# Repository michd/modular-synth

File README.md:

# Modular Synthesizer

My fiancee and I plan to build a modular synthesizer, for fun. Here's a repository to hold all kinds of stuff to do with that. I imagine it'll hold the following

- Schematic designs
- PCB designs derived from those schematic design
- Some 3D modeling for related hardware
- Any microcontroller code

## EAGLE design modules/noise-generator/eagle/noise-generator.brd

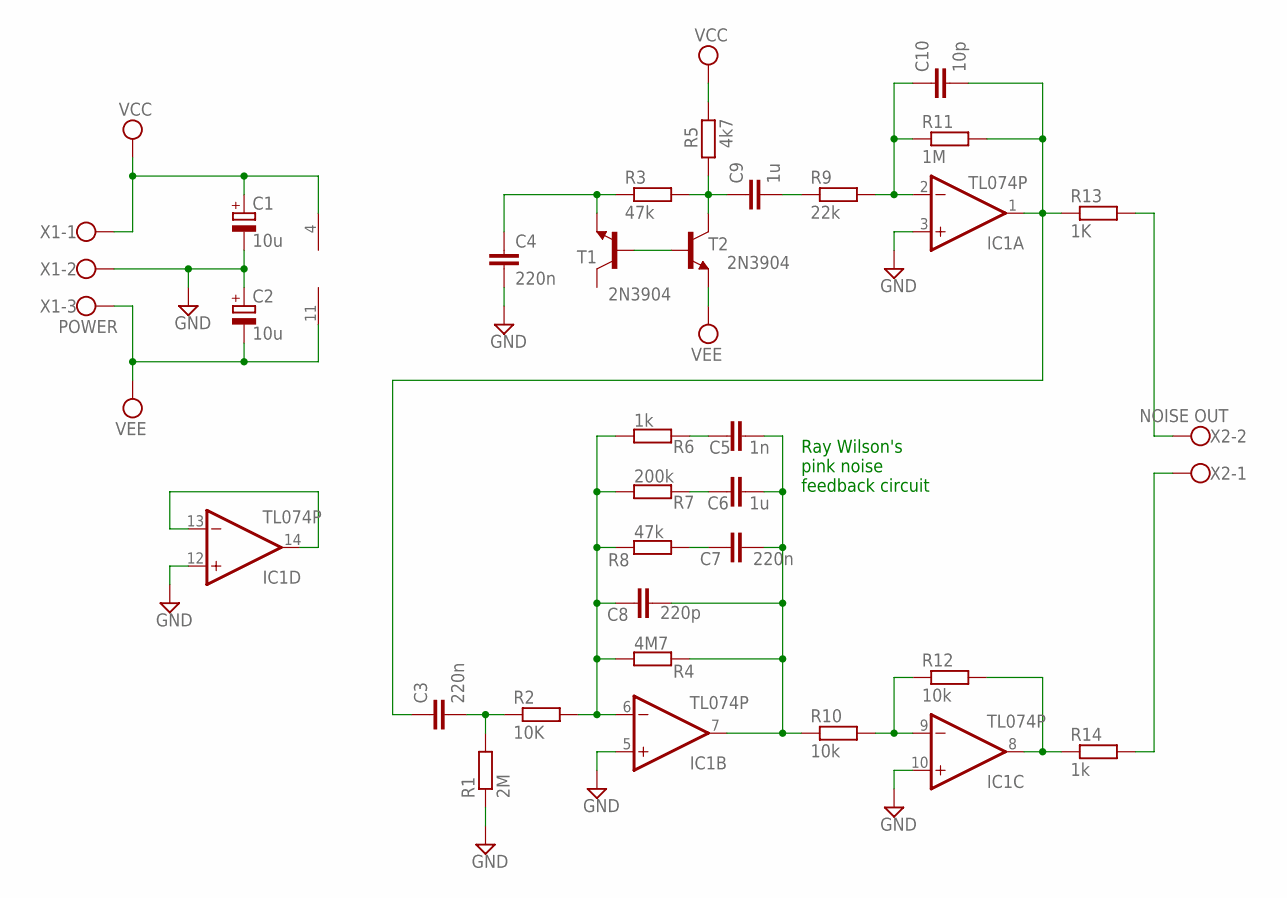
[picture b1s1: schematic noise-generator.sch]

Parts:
C1, C2: 10u; E1,8-4
C3, C4, C7: 220n; C050-024X044
C5: 1n; C050-024X044
C6, C9: 1u; C050-024X044
C8: 220p; C050-024X044
C10: 10p; C025-024X044
IC1: TL074P; DIL14
R1: 2M; 0204/7
R2: 10K; 0204/7
R3, R8: 47k; 0204/7
R4: 4M7; 0204/7
R5: 4k7; 0204/7
R6, R14: 1k; 0204/7
R7: 200k; 0204/7
R9: 22k; 0204/7
R10, R12: 10k; 0204/7
R11: 1M; 0204/7
R13: 1K; 0204/7
T1, T2: 2N3904; TO92
X1: POWER; W237-103
X2: NOISE OUT; W237-102

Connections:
GND: C1.-, C2.+, C4.2, IC1.3 (+IN), IC1.5 (+IN), IC1.10 (+IN), IC1.12 (+IN), R1.1, X1.2
unnamed: C4.1, R3.1, T1.3 (E)
unnamed: IC1.9 (-IN), R10.2, R12.1
unnamed: C9.1, R3.2, R5.1, T2.1 (C)
unnamed: T1.2 (B), T2.2 (B)
unnamed: C9.2, R9.1
unnamed: C10.1, IC1.2 (-IN), R9.2, R11.1
unnamed: R13.2, X2.2
unnamed: C3.1, C10.2, IC1.1 (OUT), R11.2, R13.1
unnamed: IC1.8 (OUT), R12.2, R14.1
unnamed: R14.2, X2.1
unnamed: C8.1, IC1.6 (-IN), R2.2, R4.1, R6.1, R7.1, R8.1
unnamed: C3.2, R1.2, R2.1
unnamed: IC1.13 (-IN), IC1.14 (OUT)
unnamed: C6.1, R7.2
unnamed: C5.1, R6.2
unnamed: C7.1, R8.2
unnamed: C5.2, C6.2, C7.2, C8.2, IC1.7 (OUT), R4.2, R10.1
VCC: C1.+, IC1.4 (V+), R5.2, X1.1
VEE: C2.-, IC1.11 (V-), T2.3 (E), X1.3

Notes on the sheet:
Ray Wilson's pink noise feedback circuit

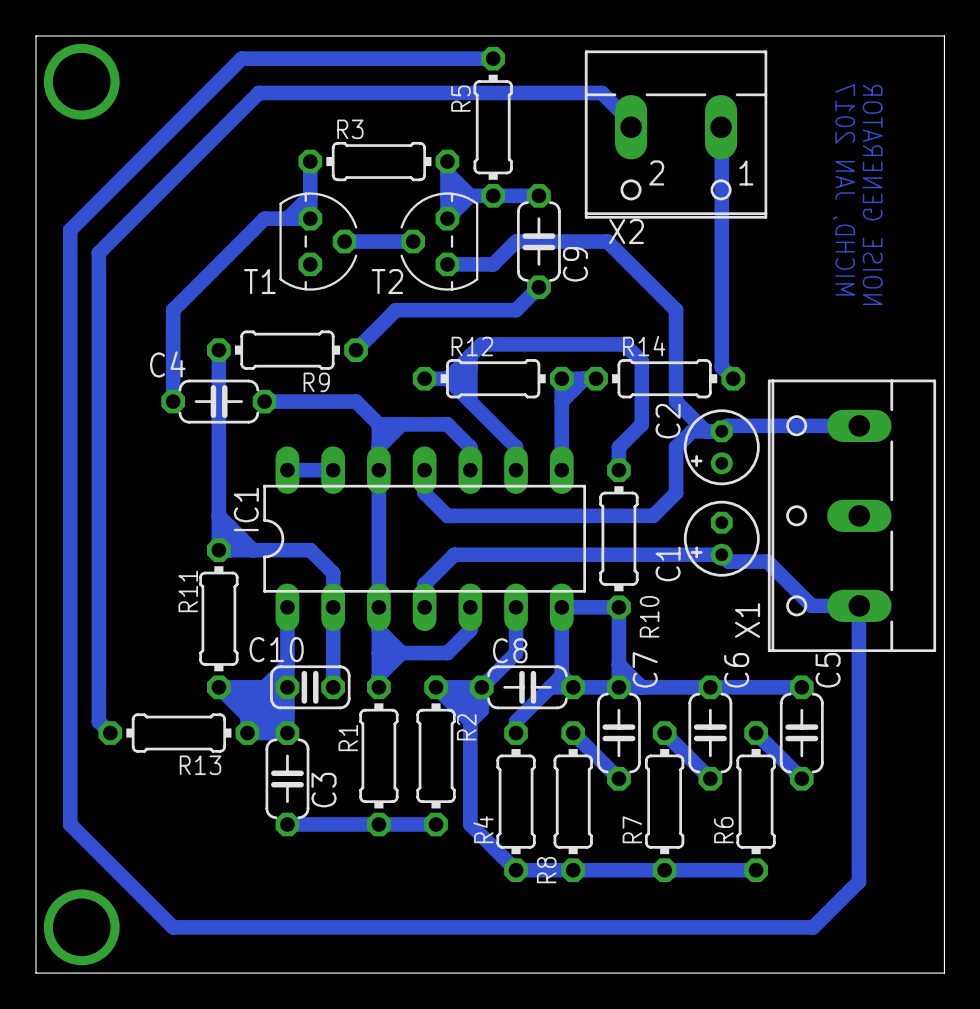
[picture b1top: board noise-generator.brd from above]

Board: 2 copper layers, 50.5 x 52.1 mm, 29 parts (0 on the bottom side), 20 nets.

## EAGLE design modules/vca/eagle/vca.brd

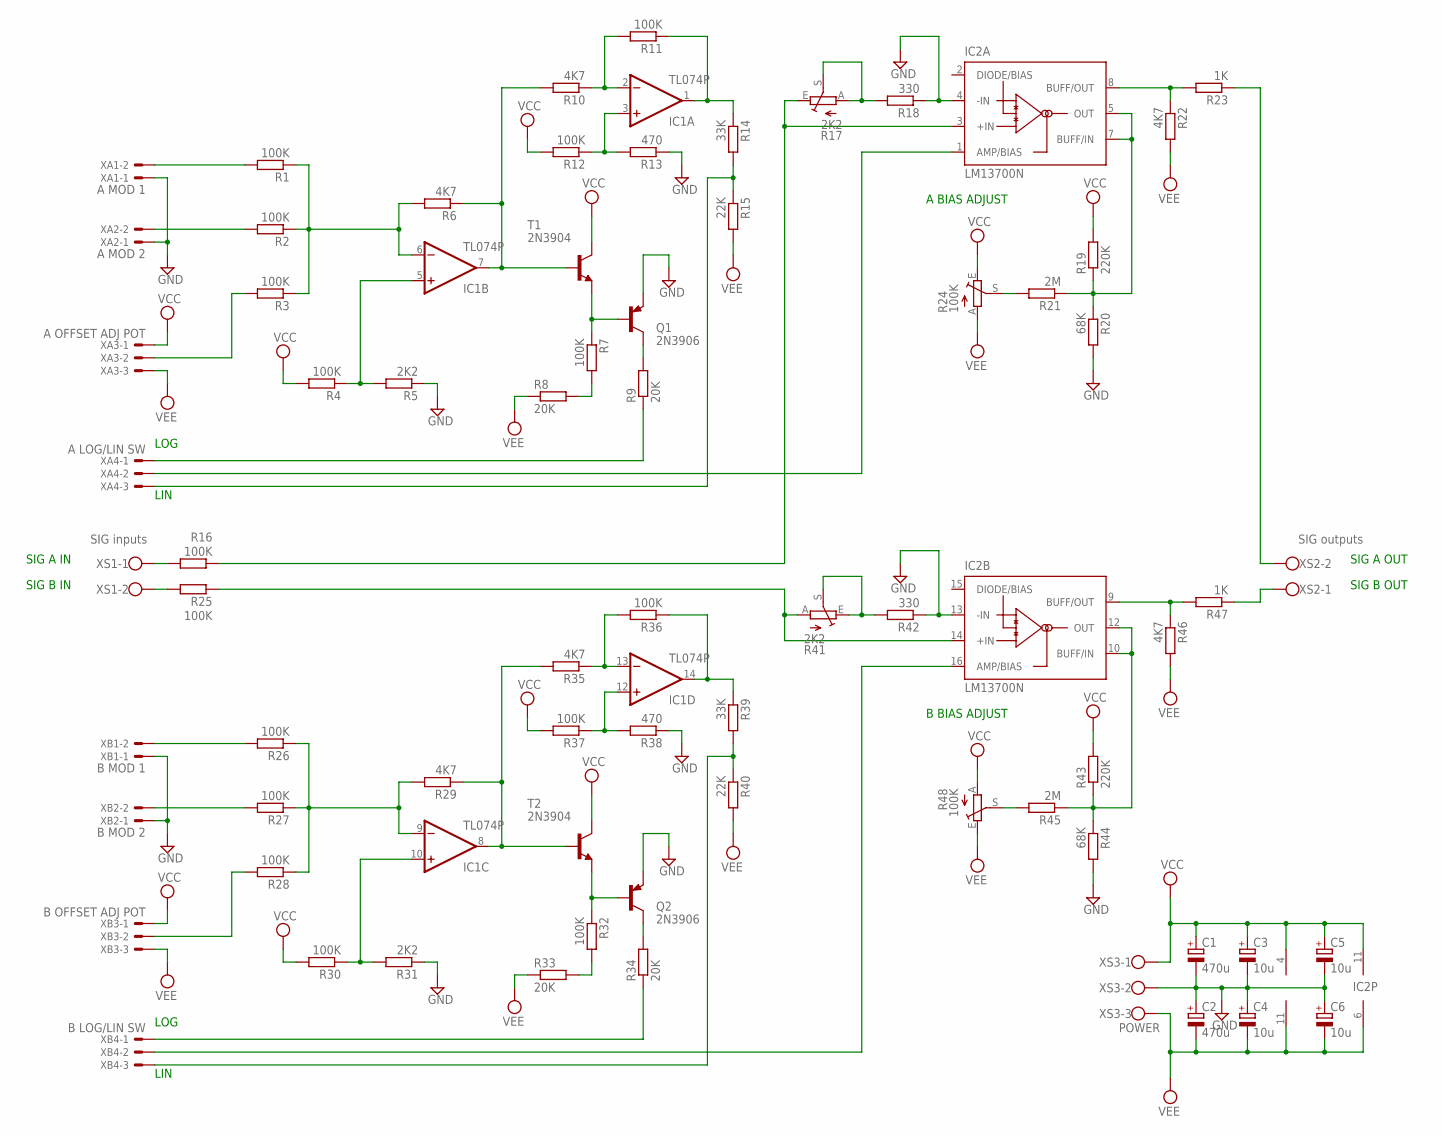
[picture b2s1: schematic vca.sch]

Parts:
C1, C2: 470u; E2,5-6
C3, C4, C5, C6: 10u; E1,8-4
IC1: TL074P; DIL14
IC2: LM13700N; DIL16
Q1, Q2: 2N3906; TO92
R1, R2, R3, R4, R7, R11, R12, R16, R25, R26, R27, R28, R30, R32, R36, R37: 100K; 0204/7
R5, R31: 2K2; 0204/7
R6, R10, R22, R29, R35, R46: 4K7; 0204/7
R8, R9, R33, R34: 20K; 0204/7
R13, R38: 470; 0204/7
R14, R39: 33K; 0204/7
R15, R40: 22K; 0204/7
R17, R41: 2K2; CA6V
R18, R42: 330; 0204/7
R19, R43: 220K; 0204/7
R20, R44: 68K; 0204/7
R21, R45: 2M; 0204/7
R23, R47: 1K; 0204/7
R24, R48: 100K; CA6V
T1, T2: 2N3904; TO92
XA1: A MOD 1; 22-23-2021
XA2: A MOD 2; 22-23-2021
XA3: A OFFSET ADJ POT; 22-23-2031
XA4: A LOG/LIN SW; 22-23-2031
XB1: B MOD 1; 22-23-2021
XB2: B MOD 2; 22-23-2021
XB3: B OFFSET ADJ POT; 22-23-2031
XB4: B LOG/LIN SW; 22-23-2031
XS1: SIG inputs; W237-102
XS2: SIG outputs; W237-102
XS3: POWER; W237-103

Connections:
GND: C1.-, C2.+, C3.-, C4.+, C5.-, C6.+, IC2.4 (-IN), IC2.13 (-IN), Q1.3 (E), Q2.3 (E), R5.1, R13.1, R18.1, R20.2, R31.1, R38.1, R42.1, R44.2, XA1.1, XA2.1, XB1.1, XB2.1, XS3.2
unnamed: IC1.6 (-IN), R1.1, R2.1, R3.1, R6.2
unnamed: R1.2, XA1.2
unnamed: R2.2, XA2.2
unnamed: R3.2, XA3.2
unnamed: IC1.5 (+IN), R4.1, R5.2
unnamed: R7.2, R8.2
unnamed: IC1.7 (OUT), R6.1, R10.2, T1.2 (B)
unnamed: Q1.2 (B), R7.1, T1.3 (E)
unnamed: Q1.1 (C), R9.2
unnamed: R9.1, XA4.1
unnamed: IC1.2 (-IN), R10.1, R11.2
unnamed: IC2.1 (AMP/BIAS), XA4.2
unnamed: IC1.1 (OUT), R11.1, R14.1
unnamed: IC2.3 (+IN), R16.1, R17.E
unnamed: IC1.3 (+IN), R12.1, R13.2
unnamed: R17.A, R17.S, R18.2
unnamed: R14.2, R15.1, XA4.3
unnamed: IC2.8 (BUFF/OUT), R22.1, R23.2
unnamed: R16.2, XS1.1
unnamed: R25.2, XS1.2
unnamed: R21.2, R24.S
unnamed: IC2.5 (OUT), IC2.7 (BUFF/IN), R19.1, R20.1, R21.1
unnamed: IC2.14 (+IN), R25.1, R41.A
unnamed: R26.2, XB1.2
unnamed: R23.1, XS2.2
unnamed: R27.2, XB2.2
unnamed: R28.2, XB3.2
unnamed: R34.1, XB4.1
unnamed: R47.1, XS2.1
unnamed: IC2.16 (AMP/BIAS), XB4.2
unnamed: IC1.9 (-IN), R26.1, R27.1, R28.1, R29.2
unnamed: IC1.8 (OUT), R29.1, R35.2, T2.2 (B)
unnamed: IC1.10 (+IN), R30.1, R31.2
unnamed: Q2.2 (B), R32.1, T2.3 (E)
unnamed: R32.2, R33.2
unnamed: Q2.1 (C), R34.2
unnamed: IC1.13 (-IN), R35.1, R36.2
unnamed: IC1.14 (OUT), R36.1, R39.1
unnamed: IC1.12 (+IN), R37.1, R38.2
unnamed: R39.2, R40.1, XB4.3
unnamed: R41.E, R41.S, R42.2
unnamed: R45.2, R48.S
unnamed: IC2.9 (BUFF/OUT), R46.1, R47.2
unnamed: IC2.10 (BUFF/IN), IC2.12 (OUT), R43.1, R44.1, R45.1
VCC: C1.+, C3.+, C5.+, IC1.4 (V+), IC2.11 (V+), R4.2, R12.2, R19.2, R24.E, R30.2, R37.2, R43.2, R48.A, T1.1 (C), T2.1 (C), XA3.1, XB3.1, XS3.1
VEE: C2.-, C4.-, C6.-, IC1.11 (V-), IC2.6 (V-), R8.1, R15.2, R22.2, R24.A, R33.1, R40.2, R46.2, R48.E, XA3.3, XB3.3, XS3.3

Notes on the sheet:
LOG
LIN
SIG A IN
SIG A OUT
A BIAS ADJUST
SIG B OUT
B BIAS ADJUST
SIG B IN

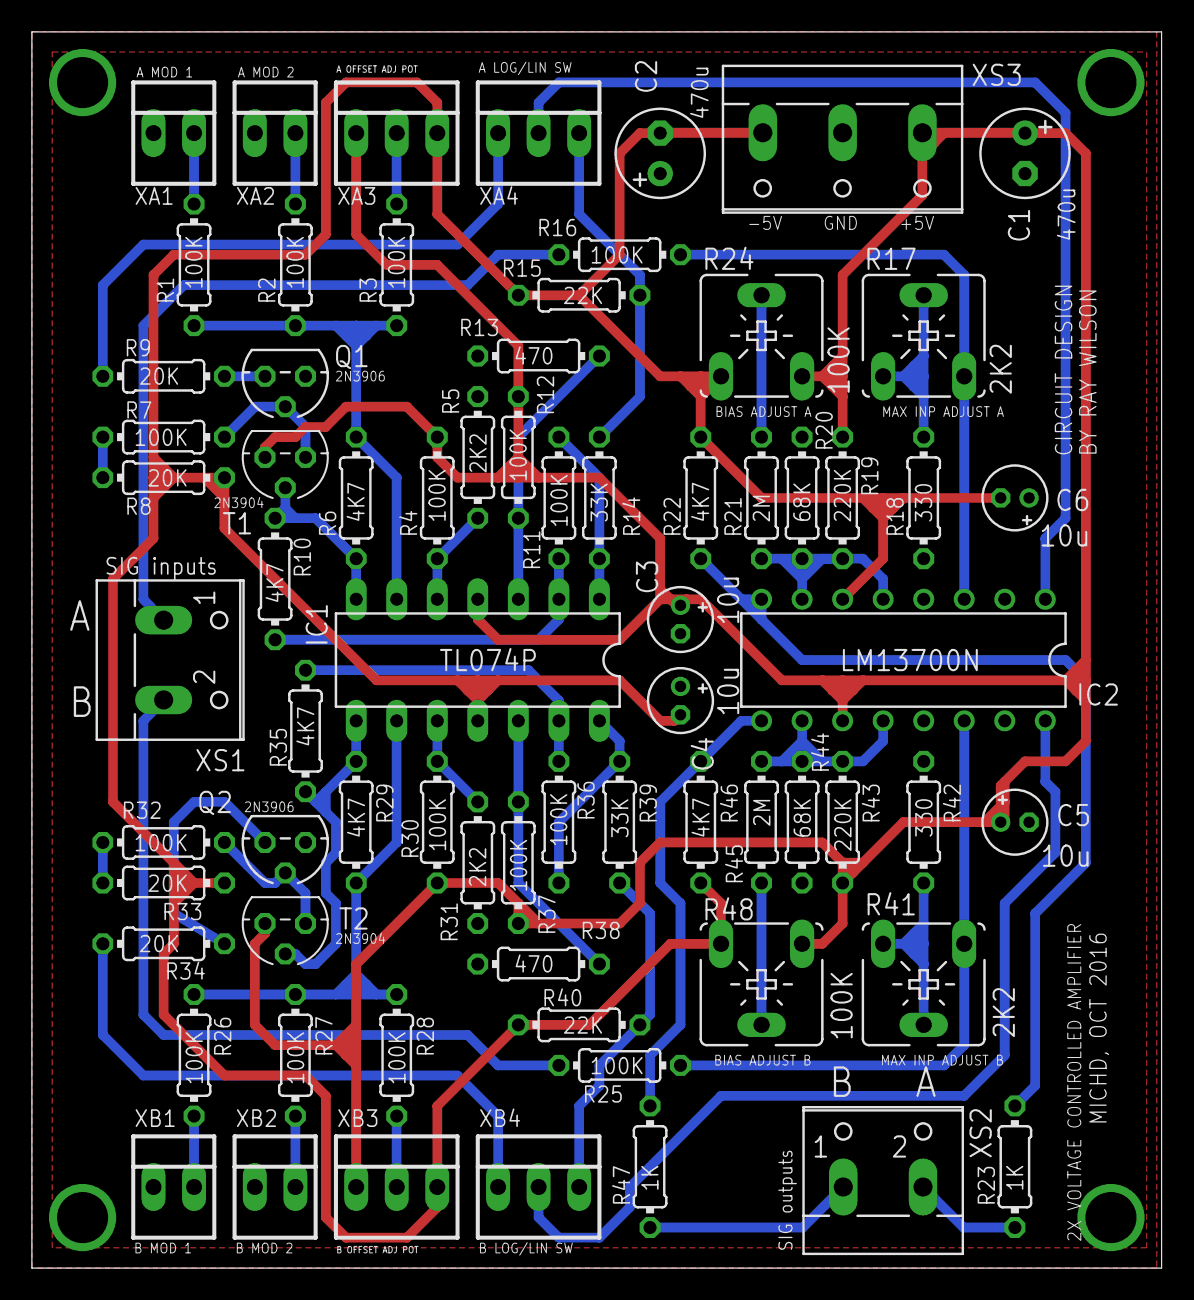
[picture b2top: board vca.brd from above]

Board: 2 copper layers, 70.8 x 77.5 mm, 71 parts (0 on the bottom side), 47 nets.

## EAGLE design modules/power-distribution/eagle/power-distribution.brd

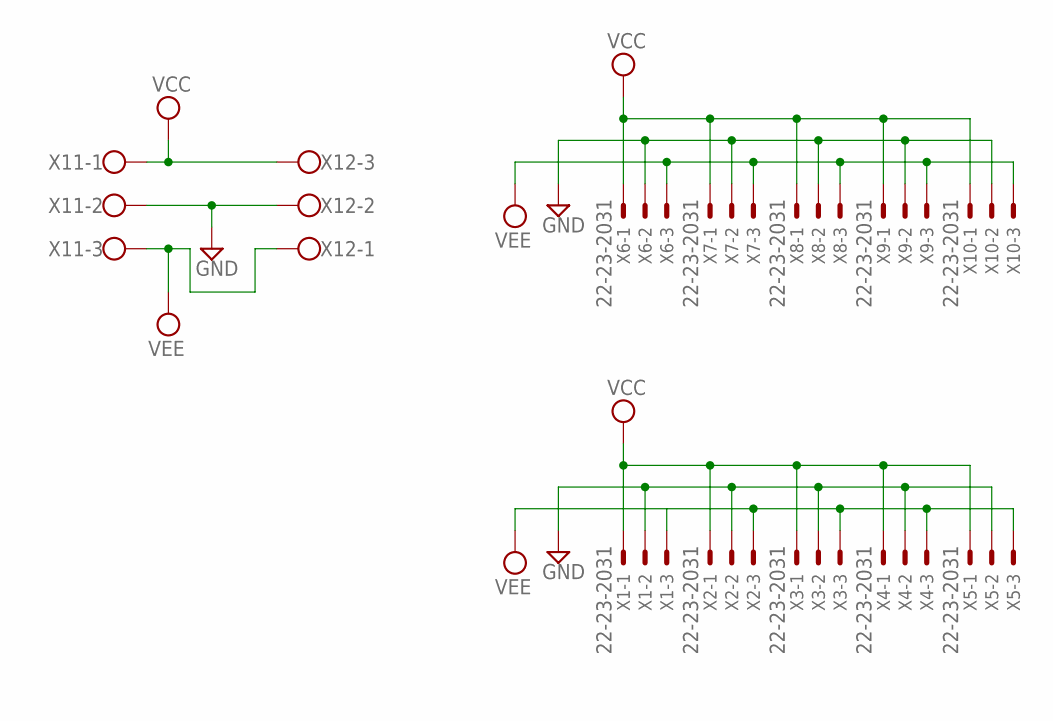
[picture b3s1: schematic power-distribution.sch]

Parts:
X1, X2, X3, X4, X5, X6, X7, X8, X9, X10: 22-23-2031
X11, X12: W237-103

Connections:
GND: X1.2, X2.2, X3.2, X4.2, X5.2, X6.2, X7.2, X8.2, X9.2, X10.2, X11.2, X12.2
VCC: X1.1, X2.1, X3.1, X4.1, X5.1, X6.1, X7.1, X8.1, X9.1, X10.1, X11.1, X12.3
VEE: X1.3, X2.3, X3.3, X4.3, X5.3, X6.3, X7.3, X8.3, X9.3, X10.3, X11.3, X12.1

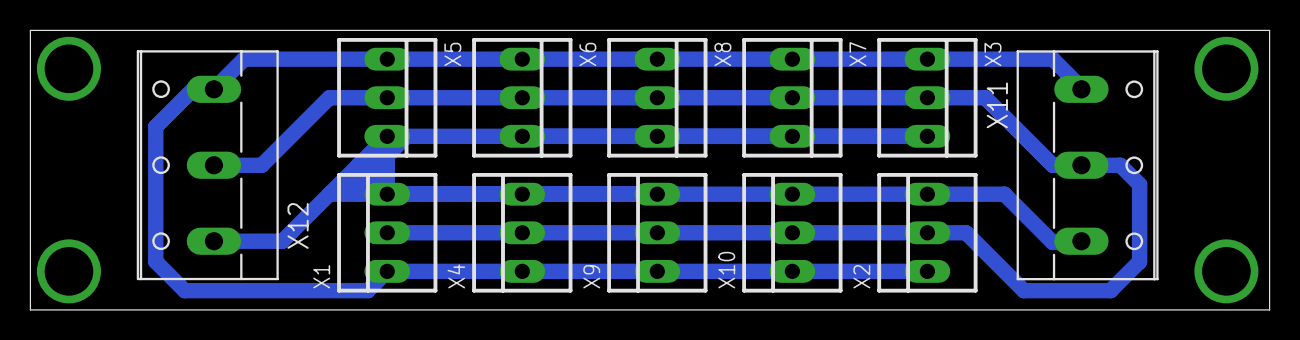
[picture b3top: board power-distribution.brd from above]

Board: 2 copper layers, 81.6 x 18.4 mm, 12 parts (0 on the bottom side), 3 nets.

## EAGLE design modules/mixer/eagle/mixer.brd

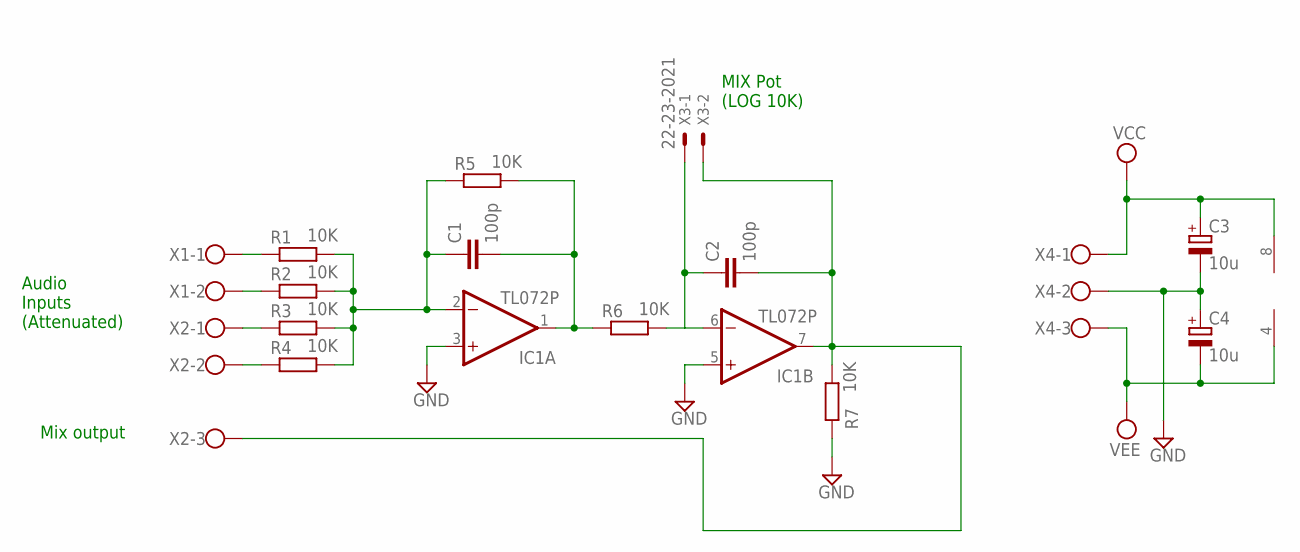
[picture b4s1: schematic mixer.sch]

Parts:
C1, C2: 100p; C025-024X044
C3, C4: 10u; E1,8-4
IC1: TL072P; DIL08
R1, R2, R3, R4, R5, R6, R7: 10K; 0204/7
X1: W237-102
X2, X4: W237-103
X3: 22-23-2021

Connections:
GND: C3.-, C4.+, IC1.3 (+IN), IC1.5 (+IN), R7.1, X4.2
unnamed: R1.1, X1.1
unnamed: R2.1, X1.2
unnamed: R3.1, X2.1
unnamed: R4.1, X2.2
unnamed: C1.1, IC1.2 (-IN), R1.2, R2.2, R3.2, R4.2, R5.1
unnamed: C1.2, IC1.1 (OUT), R5.2, R6.1
unnamed: C2.1, IC1.6 (-IN), R6.2, X3.1
unnamed: C2.2, IC1.7 (OUT), R7.2, X2.3, X3.2
VCC: C3.+, IC1.8 (V+), X4.1
VEE: C4.-, IC1.4 (V-), X4.3

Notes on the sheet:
Audio Inputs (Attenuated)
Mix output
MIX Pot (LOG 10K)

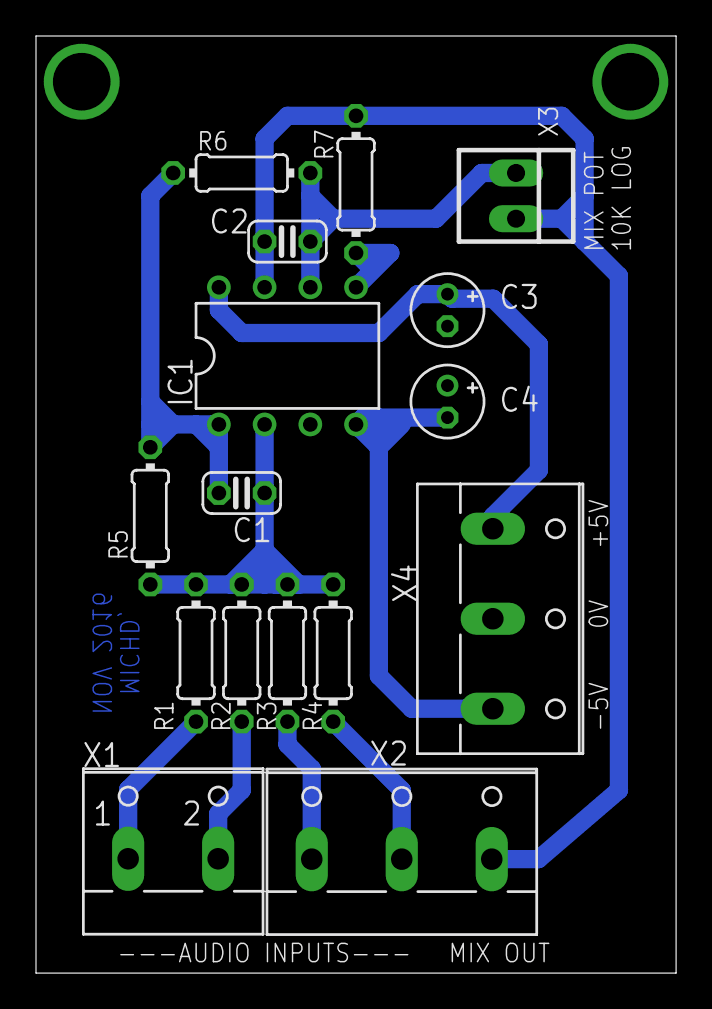
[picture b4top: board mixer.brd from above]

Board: 2 copper layers, 35.6 x 52.1 mm, 16 parts (0 on the bottom side), 11 nets.

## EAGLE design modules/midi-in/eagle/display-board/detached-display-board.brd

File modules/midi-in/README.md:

# MIDI in module

## Printed circuit boards

### Display board

#### Dimensions

Board width: 101.6mm (4")
Board height: 63.5mm (2.5")

Screw diameter: 3mm

Screw positions from bottom left (X,Y):

  - 5.08mm, 5.08mm
  - 5.08mm, 58.42mm
  - 96.52mm, 58.42mm
  - 96.52mm, 5.08mm

Summarized, the 4 screws are offset 5.08mm (.2") from the sides.

This makes them span a rectangle of 81.28mm x 43.18mm (3.2" x 1.7")

#### Part list

- R1-16: 220 Ohm 1/8W, 5% tolerance resistor
- R17, R18: 10 KOhm 1/8W, 5% tolerance resistor
- T1: BC547C NPN Transistor
- C1: 100 nF ceramic capacitor (can be replaced with electrolytic too)
- D1, D2: TDSG5150 or equivalent Common Anode 7 segment display
- V1, V2: 74595 8-bit shift register
- SV1: Standard .100" pitch pin header, or leave empty to solder wires directly to board

#### Description

The display board houses two 7-segment LED displays, to display the currently selected MIDI channel.

The shift registers on the board keep hold of the digits being displayed, and are fed data by the microcontroller on the main board.

R1-16 are current-limiting resistors for each of the 8 LEDs per display.

The transistor circuit connected to the shift registers' reset pins causes the registers to reset when the circuit is being powered up. The registers' reset pin needs to be held low (0V) in order to reset. On power-up, C1 has no charge. A current will flow "through" C1 and R18 (10K), causing a voltage drop across R18. Having the voltage drop across R18 brings the point connected to the reset pins (junction between R18 and C1) to 0V, resetting the shift registers. Once the capacitor is charged enough, the voltage drop has shifted to be across C1, and the reset pins are back to 5V, meaning the registers are no longer being reset. Normal operation can begin.

[Fun fact: while writing that power-up description I noticed I designed it wrong in the schematic: I'd be shorting VCC to GND through T1, blowing up the transistor. Documenting is good.]

### MIDI In board

#### Dimensions (identical to display board)

Board width: 101.6mm (4")
Board height: 63.5mm (2.5")

Screw diameter: 3mm

Screw positions from bottom left (X,Y):

  - 5.08mm, 5.08mm
  - 5.08mm, 58.42mm
  - 96.52mm, 58.42mm
  - 96.52mm, 5.08mm

Summarized, the 4 screws are offset 5.08mm (.2") from the sides.

This makes them span a rectangle of 81.28mm x 43.18mm (3.2" x 1.7")

#### Part list

- R1: 1 KOhm 1/8W, 5% tolerance resistor
- R2, R3, R5: 220 Ohm 1/8W, 5% tolerance resistor
- R4, R8-12: 10 KOhm 1/8W, 5% tolerance resistor
- D1: 1N4148 Diode
- C1-6: 100 nF ceramic capacitor
- OK1: 6N137 optocoupler (Should be able to drop in 6N138 or 6N139 without further changes)
- IC1: LM358 Dual single-supply opamp (even though we're only using one)
- SV1, SV2: Standard .100" 12-pin female pin header
- X1, X6: .200" pitch connector, or leave empty to solder wires directly to board
- X2-4, JP1: .100" pitch connector, or leave empty to solder wires directly to board

#### Description

The MIDI in board uses an opto-coupler (OK1) to electrically isolate the MIDI input signal from our circuit. Its input is buffered through an opamp (IC1) and connected back to the MIDI Thru connector, to allow daisy-chaining.

The circuit houses an Arduino Pro Micro, plugged into female pin headers SV1 and SV2. The filtered MIDI signal (serial data) is fed into the RX pin of the Arduino. The Arduino is programmed to only listen to one of the available MIDI channels, and the selected channel is to be displayed on 7-segment displays. The software listens for MIDI status messages, and updates 7 outputs
based on this data.

The 7 segment displays are on the display board where shift registers drive them. The serial data is clocked through by the Arduino, and is hooked up through connector X5.

There is an input for a momentary push button (push to make contact), which lets you change the MIDI channel listened for. Pushing the button shorts the relevant pin to ground, where it's normally high at 5V.

The main outputs are the logic "gate" and "trigger", and the analog "FreqCV". Gate is high as long as at least one note is pressed. Trigger pulses high for 1ms whenever a new note is pressed. These are intended to be used by envelope generators later. FreqCV is destined for an analog voltage where a difference of 1V represents a difference of 1 octave in sound frequency. At the output here though, it's still just in the arduino's output range of 0-5V.

Further, there are 4 additional analog outputs, MOD1-4. They also come out as 0-5V from this board.

All the analog outputs on here come from a pulse width modulation (PWM) signal generated by the arduino. A passive low pass filter comprised of a 100nF capacitor and a 10K resistor is connected to each of them, to normalize the PWM to an analog voltage.

All these outputs will be connected to the CV (control voltage) board, where the voltage ranges get scaled to appropriate levels (including fine-tuning through trimpots).

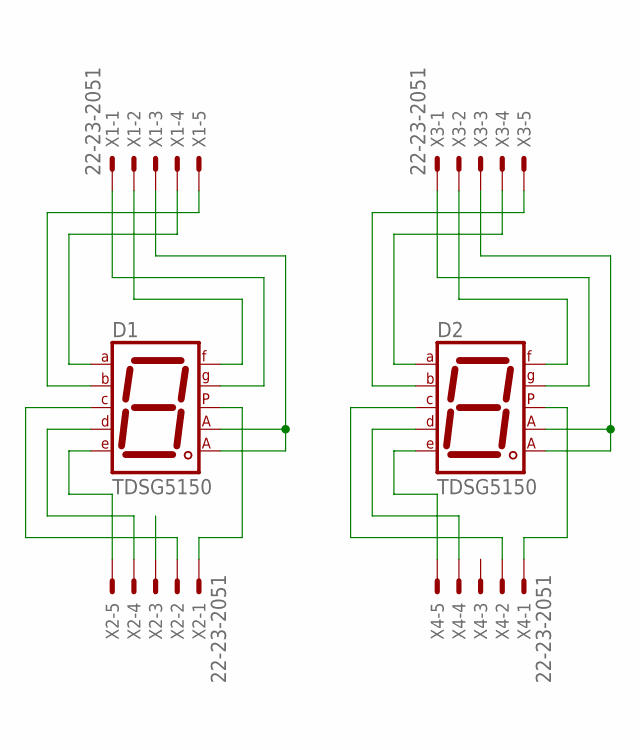
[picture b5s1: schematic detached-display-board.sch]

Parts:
D1, D2: TDSG5150; 7SEG-13
X1, X2, X3, X4: 22-23-2051

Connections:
unnamed: D1.1 (E), X2.5
unnamed: D1.2 (D), X2.4
unnamed: D2.1 (E), X4.5
unnamed: D2.2 (D), X4.4
unnamed: D1.4 (C), X2.2
unnamed: D1.5 (DP), X2.1
unnamed: D2.4 (C), X4.2
unnamed: D2.5 (DP), X4.1
unnamed: D1.10 (G), X1.1
unnamed: D2.10 (G), X3.1
unnamed: D1.9 (F), X1.2
unnamed: D2.9 (F), X3.2
unnamed: D1.3 (CA1), D1.8 (CA2), X1.3
unnamed: D2.3 (CA1), D2.8 (CA2), X3.3
unnamed: D1.7 (A), X1.4
unnamed: D2.7 (A), X3.4
unnamed: D1.6 (B), X1.5
unnamed: D2.6 (B), X3.5

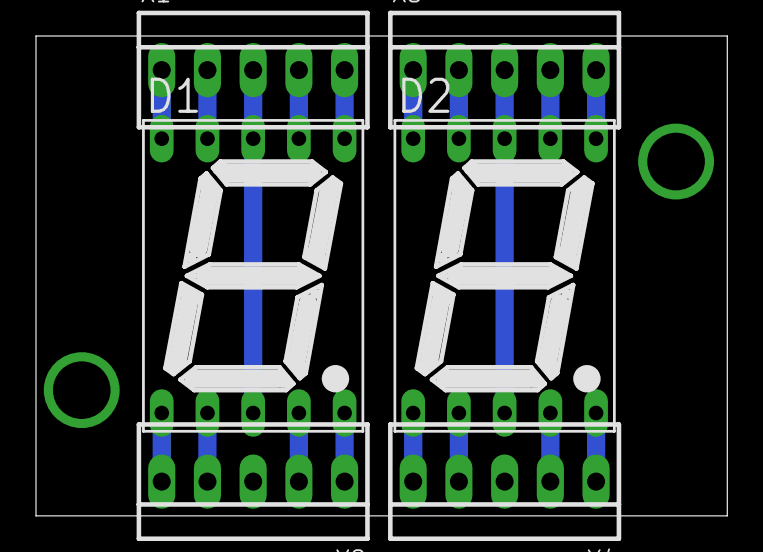
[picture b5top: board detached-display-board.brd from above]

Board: 2 copper layers, 38.4 x 26.7 mm, 6 parts (0 on the bottom side), 18 nets.

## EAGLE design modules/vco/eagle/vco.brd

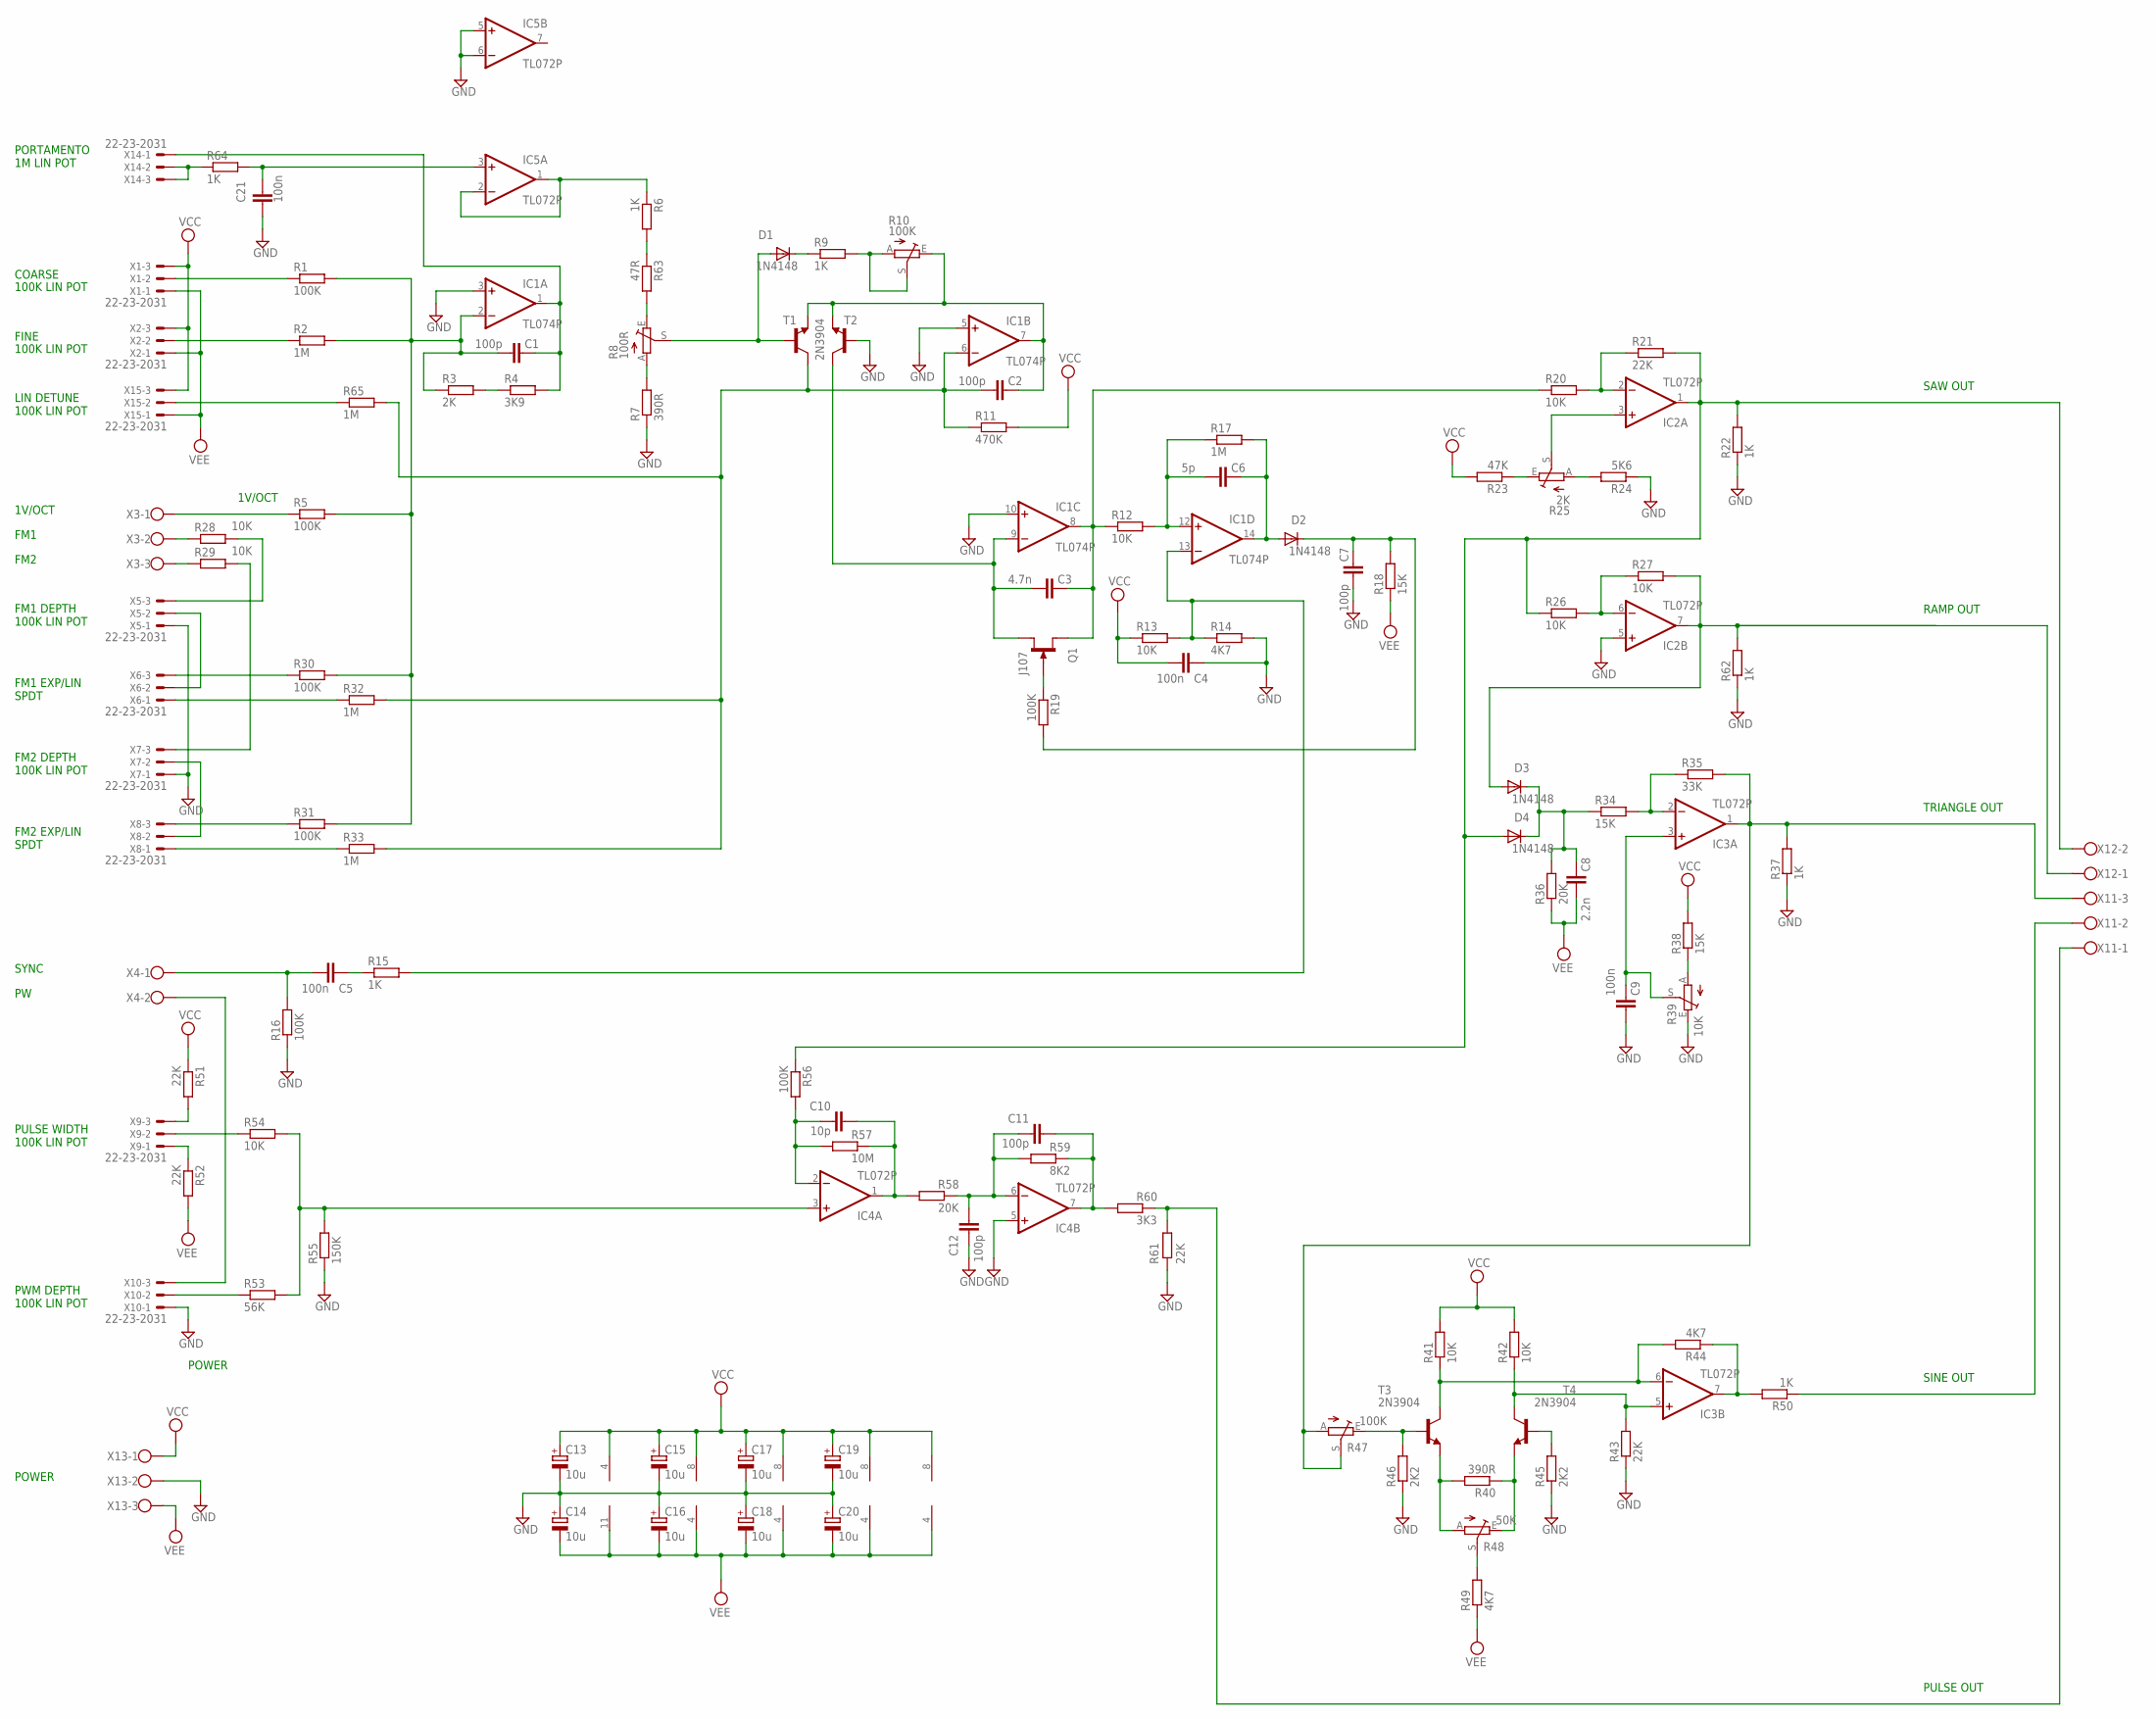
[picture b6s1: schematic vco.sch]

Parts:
C1, C2, C7, C11, C12: 100p; C025-024X044
C3: 4.7n; C025-024X044
C4, C5, C9, C21: 100n; C025-024X044
C6: 5p; C025-024X044
C8: 2.2n; C025-024X044
C10: 10p; C025-024X044
C13, C14, C15, C16, C17, C18, C19, C20: 10u; E1,8-4
D1, D2, D3, D4: 1N4148; DO35-7
IC1: TL074P; DIL14
IC2, IC3, IC4, IC5: TL072P; DIL08
Q1: J107; TO92R
R1, R5, R16, R19, R30, R31, R56: 100K; 0204/7
R2, R17, R32, R33, R65: 1M; 0204/7
R3: 2K; 0309/12
R4: 3K9; 0204/7
R6, R9, R15, R22, R37, R50, R62, R64: 1K; 0204/7
R7, R40: 390R; 0204/7
R8: 100R; B64Y
R10: 100K; B64Y
R11: 470K; 0204/7
R12, R13, R20, R26, R27, R28, R29, R41, R42, R54: 10K; 0204/7
R14, R44, R49: 4K7; 0204/7
R18, R34, R38: 15K; 0204/7
R21, R43, R51, R52, R61: 22K; 0204/7
R23: 47K; 0204/7
R24: 5K6; 0204/7
R25: 2K; B64Y
R35: 33K; 0204/7
R36, R58: 20K; 0204/7
R39: 10K; CA6V
R45, R46: 2K2; 0204/7
R47: 100K; CA6V
R48: 50K; CA6V
R53: 56K; 0204/7
R55: 150K; 0204/7
R57: 10M; 0204/7
R59: 8K2; 0204/7
R60: 3K3; 0204/7
R63: 47R; 0204/7
T1, T2, T3, T4: 2N3904; TO92
X1, X2, X5, X6, X7, X8, X9, X10, X14, X15: 22-23-2031
X3, X11, X13: W237-103
X4, X12: W237-102

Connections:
GND: C4.1, C7.2, C9.2, C12.1, C13.-, C14.+, C15.-, C16.+, C17.-, C18.+, C19.-, C20.+, C21.2, IC1.3 (+IN), IC1.5 (+IN), IC1.10 (+IN), IC2.5 (+IN), IC4.5 (+IN), IC5.5 (+IN), IC5.6 (-IN), R7.1, R14.2, R16.1, R22.1, R24.1, R37.1, R39.E, R43.1, R45.1, R46.1, R55.1, R61.1, R62.1, T2.2 (B), X5.1, X7.1, X10.1, X13.2
unnamed: R1.1, X1.2
unnamed: C1.1, IC1.1 (OUT), R4.2, X14.1
unnamed: R3.2, R4.1
unnamed: R6.2, R63.1
unnamed: R7.2, R8.A
unnamed: C2.1, IC1.7 (OUT), R10.E, T1.3 (E), T2.3 (E)
unnamed: D1.A, R8.S, T1.2 (B)
unnamed: D1.C, R9.1
unnamed: R9.2, R10.A, R10.S
unnamed: C6.2, IC1.12 (+IN), R12.2, R17.1
unnamed: IC1.13 (-IN), R13.2, R14.1, R15.2
unnamed: C10.1, IC4.2 (-IN), R56.2, R57.1
unnamed: C3.2, IC1.9 (-IN), Q1.S, T2.1 (C)
unnamed: C3.1, IC1.8 (OUT), Q1.D, R12.1, R20.1
unnamed: C7.1, D2.C, R18.2, R19.2
unnamed: C5.1, R15.1
unnamed: C5.2, R16.2, X4.1
unnamed: C6.1, D2.A, IC1.14 (OUT), R17.2
unnamed: R23.1, R25.E
unnamed: Q1.G, R19.1
unnamed: R24.2, R25.A
unnamed: IC2.2 (-IN), R20.2, R21.1
unnamed: R2.1, X2.2
unnamed: IC3.2 (-IN), R34.2, R35.1
unnamed: IC2.3 (+IN), R25.S
unnamed: IC2.6 (-IN), R26.2, R27.1
unnamed: R28.1, X3.2
unnamed: R5.1, X3.1
unnamed: R29.1, X3.3
unnamed: R29.2, X7.3
unnamed: R28.2, X5.3
unnamed: X5.2, X6.2
unnamed: X7.2, X8.2
unnamed: R30.1, X6.3
unnamed: R31.1, X8.3
unnamed: R32.1, X6.1
unnamed: R33.1, X8.1
unnamed: R52.1, X9.1
unnamed: C8.1, D3.C, D4.C, R34.1, R36.2
unnamed: R51.2, X9.3
unnamed: R54.1, X9.2
unnamed: R38.1, R39.A
unnamed: C9.1, IC3.3 (+IN), R39.S
unnamed: R40.2, R48.A, T3.3 (E)
unnamed: R40.1, R48.E, T4.3 (E)
unnamed: IC3.6 (-IN), R41.1, R44.2, T3.1 (C)
unnamed: IC3.5 (+IN), R42.1, R43.2, T4.1 (C)
unnamed: X4.2, X10.3
unnamed: C10.2, IC4.1 (OUT), R57.2, R58.1
unnamed: IC3.7 (OUT), R44.1, R50.2
unnamed: R45.2, T4.2 (B)
unnamed: R46.2, R47.E, T3.2 (B)
unnamed: C11.1, C12.2, IC4.6 (-IN), R58.2, R59.1
unnamed: C11.2, IC4.7 (OUT), R59.2, R60.1
unnamed: R48.S, R49.2
unnamed: R8.E, R63.2
unnamed: R64.1, X14.2, X14.3
unnamed: C21.1, IC5.3 (+IN), R64.2
unnamed: IC5.1 (OUT), IC5.2 (-IN), R6.1
unnamed: R65.1, X15.2
unnamed: R53.1, X10.2
N$EXP-CV1: C1.2, IC1.2 (-IN), R1.2, R2.2, R3.1, R5.2, R30.2, R31.2
N$LIN-CV1: C2.2, IC1.6 (-IN), R11.1, R32.2, R33.2, R65.2, T1.1 (C)
N$PULSE-OUT1: R60.2, R61.2, X11.1
N$PW-CV1: IC4.3 (+IN), R53.2, R54.2, R55.2
N$SAW-OUT1: D4.A, IC2.1 (OUT), R21.2, R22.2, R26.1, R56.1, X12.2
N$SAW-OUT2: D3.A, IC2.7 (OUT), R27.2, R62.2, X12.1
N$SINE-OUT1: R50.1, X11.2
N$TRI-OUT1: IC3.1 (OUT), R35.2, R37.2, R47.A, R47.S, X11.3
VCC: C4.2, C13.+, C15.+, C17.+, C19.+, IC1.4 (V+), IC2.8 (V+), IC3.8 (V+), IC4.8 (V+), IC5.8 (V+), R11.2, R13.1, R23.2, R38.2, R41.2, R42.2, R51.1, X1.3, X2.3, X13.1, X15.3
VEE: C8.2, C14.-, C16.-, C18.-, C20.-, IC1.11 (V-), IC2.4 (V-), IC3.4 (V-), IC4.4 (V-), IC5.4 (V-), R18.1, R36.1, R49.1, R52.2, X1.1, X2.1, X13.3, X15.1

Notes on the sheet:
COARSE
FINE
1V/OCT
SAW OUT
RAMP OUT
100K LIN POT
FM1
FM2
SYNC
FM1 DEPTH 100K LIN POT
FM2 DEPTH 100K LIN POT
FM1 EXP/LIN SPDT
FM2 EXP/LIN SPDT
TRIANGLE OUT
SINE OUT
PULSE WIDTH 100K LIN POT
PWM DEPTH 100K LIN POT
PULSE OUT
POWER
PORTAMENTO 1M LIN POT
LIN DETUNE 100K LIN POT

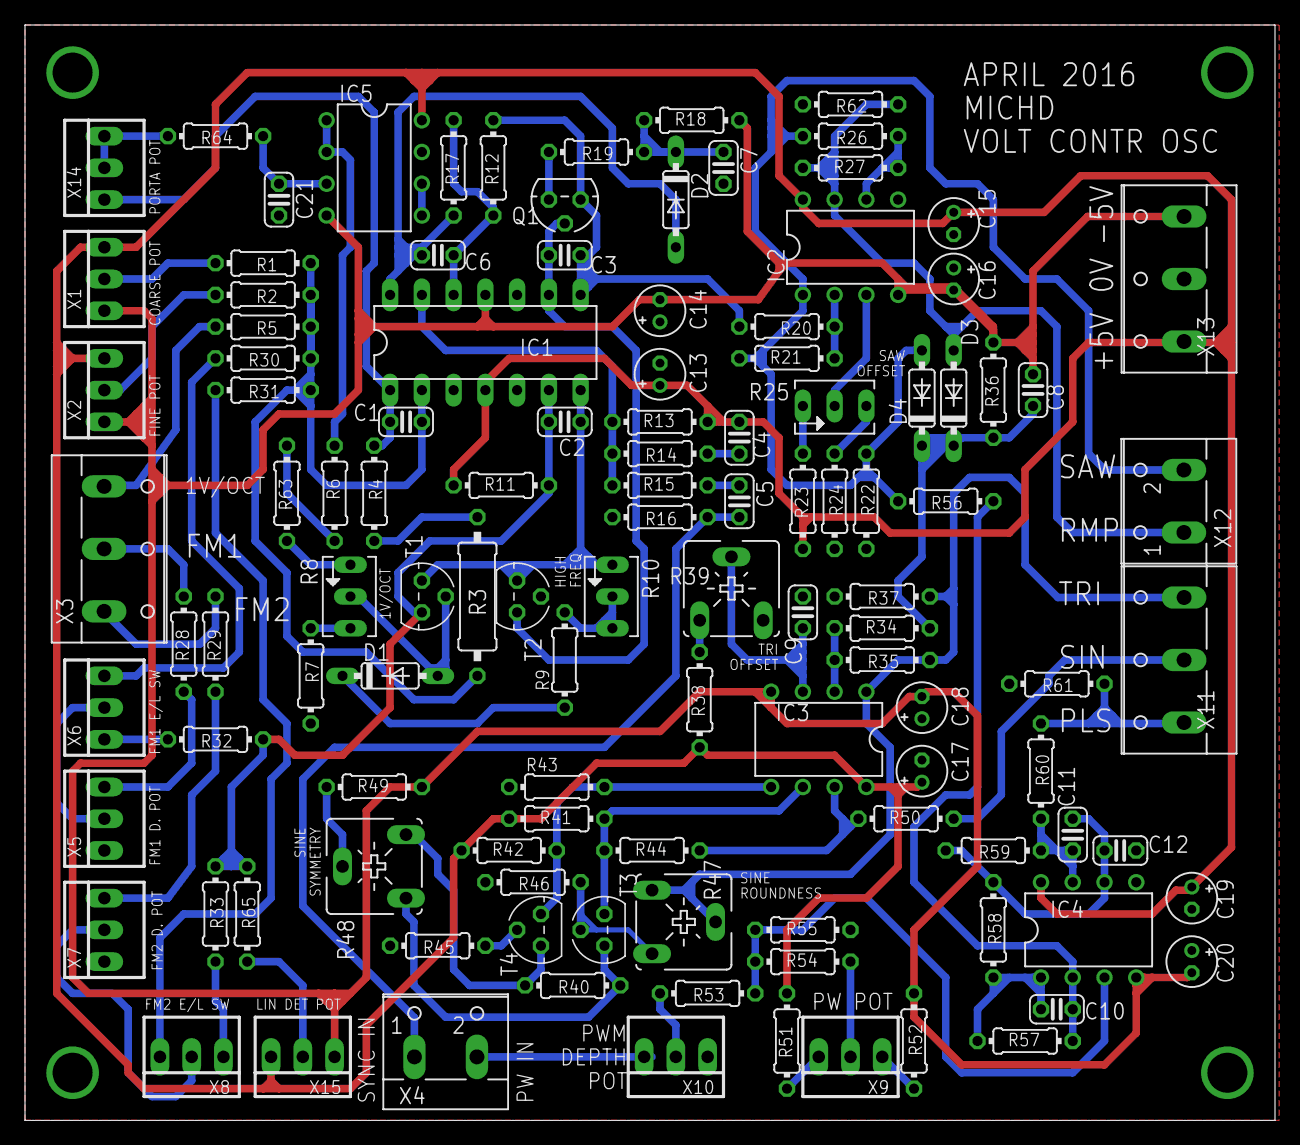
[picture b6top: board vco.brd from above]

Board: 2 copper layers, 100.0 x 87.6 mm, 115 parts (0 on the bottom side), 72 nets.
